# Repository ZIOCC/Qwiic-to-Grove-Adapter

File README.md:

# Qwiic to Grove Adapter

> This product can be available for purchase [here](https://www.smart-prototyping.com/Qwiic-to-Grove-Adapter).

#### Description

There are already lots of I2C grove modules on the market, so it is reasonable to let Gorve and Qwiic modules work together. Here is the adapter that allows you to connect Qwiic module on the one side, and the Grove I2C device on the four Grove connectors. 

> Note: This adapter is only allowed for connecting Grove I2C device on the Grove connector. 

#### Specification

* 2 Qwiic connectors
* 4 Grove connectors (only support I2C device)
* Dimension: 26.2x 30.1mm
* Weight: 3.9g

#### Links

* [PCB Source file and Gerber file](https://github.com/ZIOCC/Qwiic-to-Grove-Adapter)

###### About Zio
> Zio is a new line of open sourced, compact, and grid layout boards, fully integrated for Arduino and Qwiic ecosystem. Designed ideally for wearables, robotics, small-space limitations or other on the go projects. Check out other awesome Zio products [here](https://www.smart-prototyping.com/Zio).

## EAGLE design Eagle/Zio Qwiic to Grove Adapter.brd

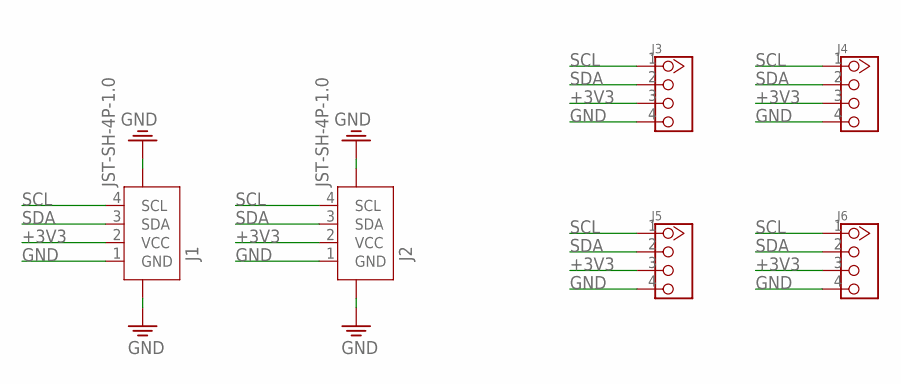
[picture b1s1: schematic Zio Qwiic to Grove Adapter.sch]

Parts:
J1, J2: JST-SH-4P-1.0; JST-SH-4P
J3, J4, J5, J6: TWIG-4P-2.0-2.0; 4P-2.0

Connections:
+3V3: J1.2 (VCC), J2.2 (VCC), J3.3, J4.3, J5.3, J6.3
GND: J1.1 (GND), J1.NC1 (5), J1.NC2 (6), J2.1 (GND), J2.NC1 (5), J2.NC2 (6), J3.4, J4.4, J5.4, J6.4
SCL: J1.4 (SCL), J2.4 (SCL), J3.1, J4.1, J5.1, J6.1
SDA: J1.3 (SDA), J2.3 (SDA), J3.2, J4.2, J5.2, J6.2

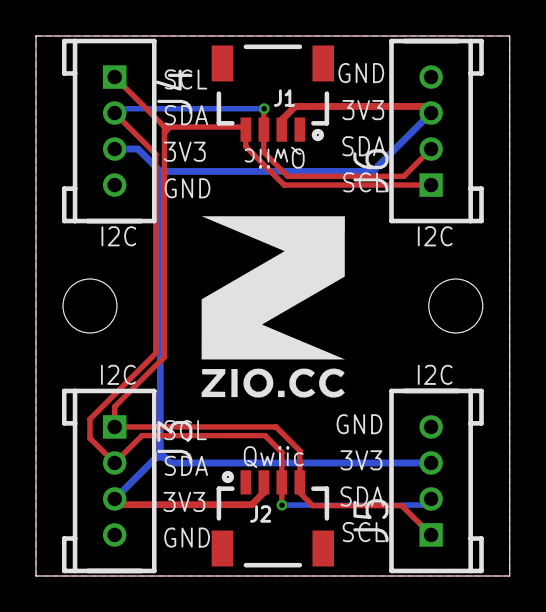
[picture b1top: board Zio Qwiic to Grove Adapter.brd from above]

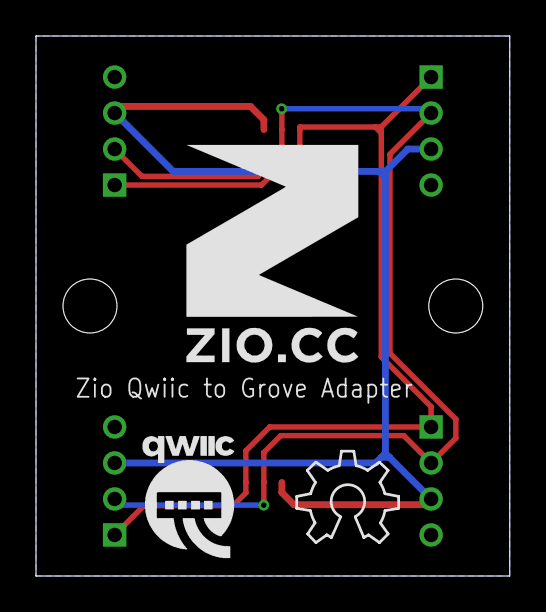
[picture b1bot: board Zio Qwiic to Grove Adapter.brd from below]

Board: 2 copper layers, 26.3 x 30.0 mm, 10 parts (3 on the bottom side), 4 nets.

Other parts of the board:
U$1: 10MM
U$2: 12MM
U$3: QWIIC-LOGO-MEDIUM
U$4: OSHW_6X200_NOTEXT
